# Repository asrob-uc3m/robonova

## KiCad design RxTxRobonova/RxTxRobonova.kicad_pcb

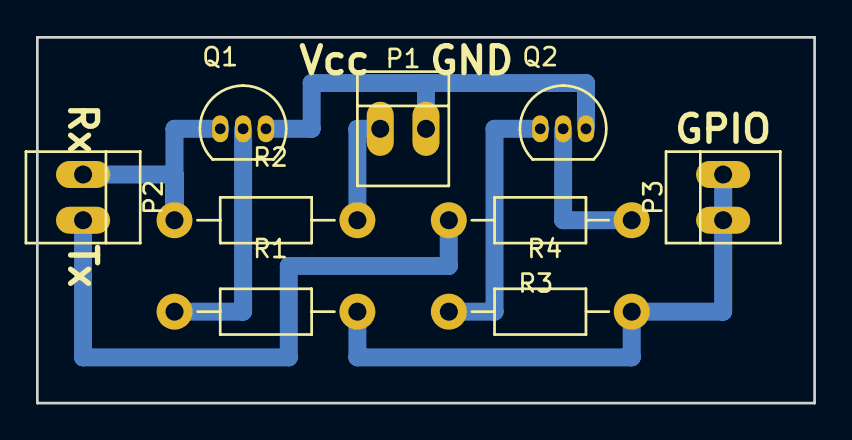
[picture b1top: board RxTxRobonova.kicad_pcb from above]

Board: 2 copper layers, 43.2 x 20.3 mm, 9 parts (0 on the bottom side), 8 nets.

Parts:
P1, P2, P3: CONN_01X02; PINHEAD1-2
Q1, Q2: Q_NPN_CBE; TO-92_Inline_Narrow_Oval
R1, R3: R; Resistor_Horizontal_RM10mm
R2: 10K; Resistor_Horizontal_RM10mm
R4: 1R; Resistor_Horizontal_RM10mm

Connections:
/GPIO: P3.1, P3.2, R1.2, R4.2
/RX: P2.1, Q1.1, R2.1
/TX: P2.2, R3.2
GND: P1.2, Q1.3, Q2.3
unnamed: Q1.2, R1.1
unnamed: Q2.1, R4.1
unnamed: Q2.2, R3.1
VCC: P1.1, R2.2

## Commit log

2015-10-13 Practicando I2C
    Programas utilizados para ilustrar el manejo de I2C con sensores:
    acelerómetro, giróscopo y brújula.
2015-10-20 Arduino con registros
2015-10-20 Modificacion basica
2015-10-20 Una tontería
2015-11-03 Primer intento de acceder a los servos por serie
2015-11-03 PCB ServoRobonova RXTX
    Pequeña plaquita que convierte RxTx en comunicación de los servos de
    Robonova. Esta pensada para poder soldar en una placa microperforada.
2017-03-02 Minor changes
